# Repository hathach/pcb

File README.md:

# pcb — PCB projects home

One repo, Adafruit-style: every board lives in its own directory here,
alongside the shared knowledge, footprints, and tooling that future
boards reuse. Board pico2_trace_motherboard's original 50-commit build
history is preserved on branch `archive/pico2-original`.

## Layout

| Entry                             | What                                                                                                                                                               |
| --------------------------------- | ------------------------------------------------------------------------------------------------------------------------------------------------------------------ |
| `pico2_trace_motherboard/`        | Board #1: Pico 2 SWD+ETM trace carrier + TinyUSB dev/test bench (RP2350, 2-layer). Ordered: JLCPCB **W2026073018593887**, 2026-07-30, 5 PCB / 2 assembled, $81.27. |
| `docs/pipeline.md`                | The netlist-driven KiCad pipeline + gate battery + how to bootstrap board #2.                                                                                      |
| `docs/kicad-pcbnew-facts.md`      | Verified KiCad 9 scripting landmines (pcbnew API, kicad-cli, footprints).                                                                                          |
| `docs/parts-palette.md`           | LCSC/JLC-verified parts with tiers + JLC fee behavior.                                                                                                             |
| `docs/PICO2_TRACE_PCB_HANDOFF.md` | Origin brief for board #1 (fly-wire measurements, requirements).                                                                                                   |
| `lib/pcb.pretty/`                 | Audited shared footprints: USB-C C165948 lands (power-only + USB2-device renumbers), FTSH-110/105 1.27mm headers. Copy into each board's local `.pretty`.          |
| `tools/jlc-cdp/`                  | Chrome-DevTools JLCPCB ordering driver + wizard-trap playbook.                                                                                                     |
| `tools/board_semantic_compare.py` | Prove two `.kicad_pcb` are geometrically identical (regen gate).                                                                                                   |
| `tools/align_md_tables.py`        | Markdown table column aligner (house style).                                                                                                                       |

## Starting a new board

Read `docs/pipeline.md` — short version: copy `pico2_trace_motherboard/hw/`
wholesale, gut the board-specific tables, keep every helper and gate, seed
footprints from `lib/pcb.pretty/`, and regenerate-never-hand-nudge.

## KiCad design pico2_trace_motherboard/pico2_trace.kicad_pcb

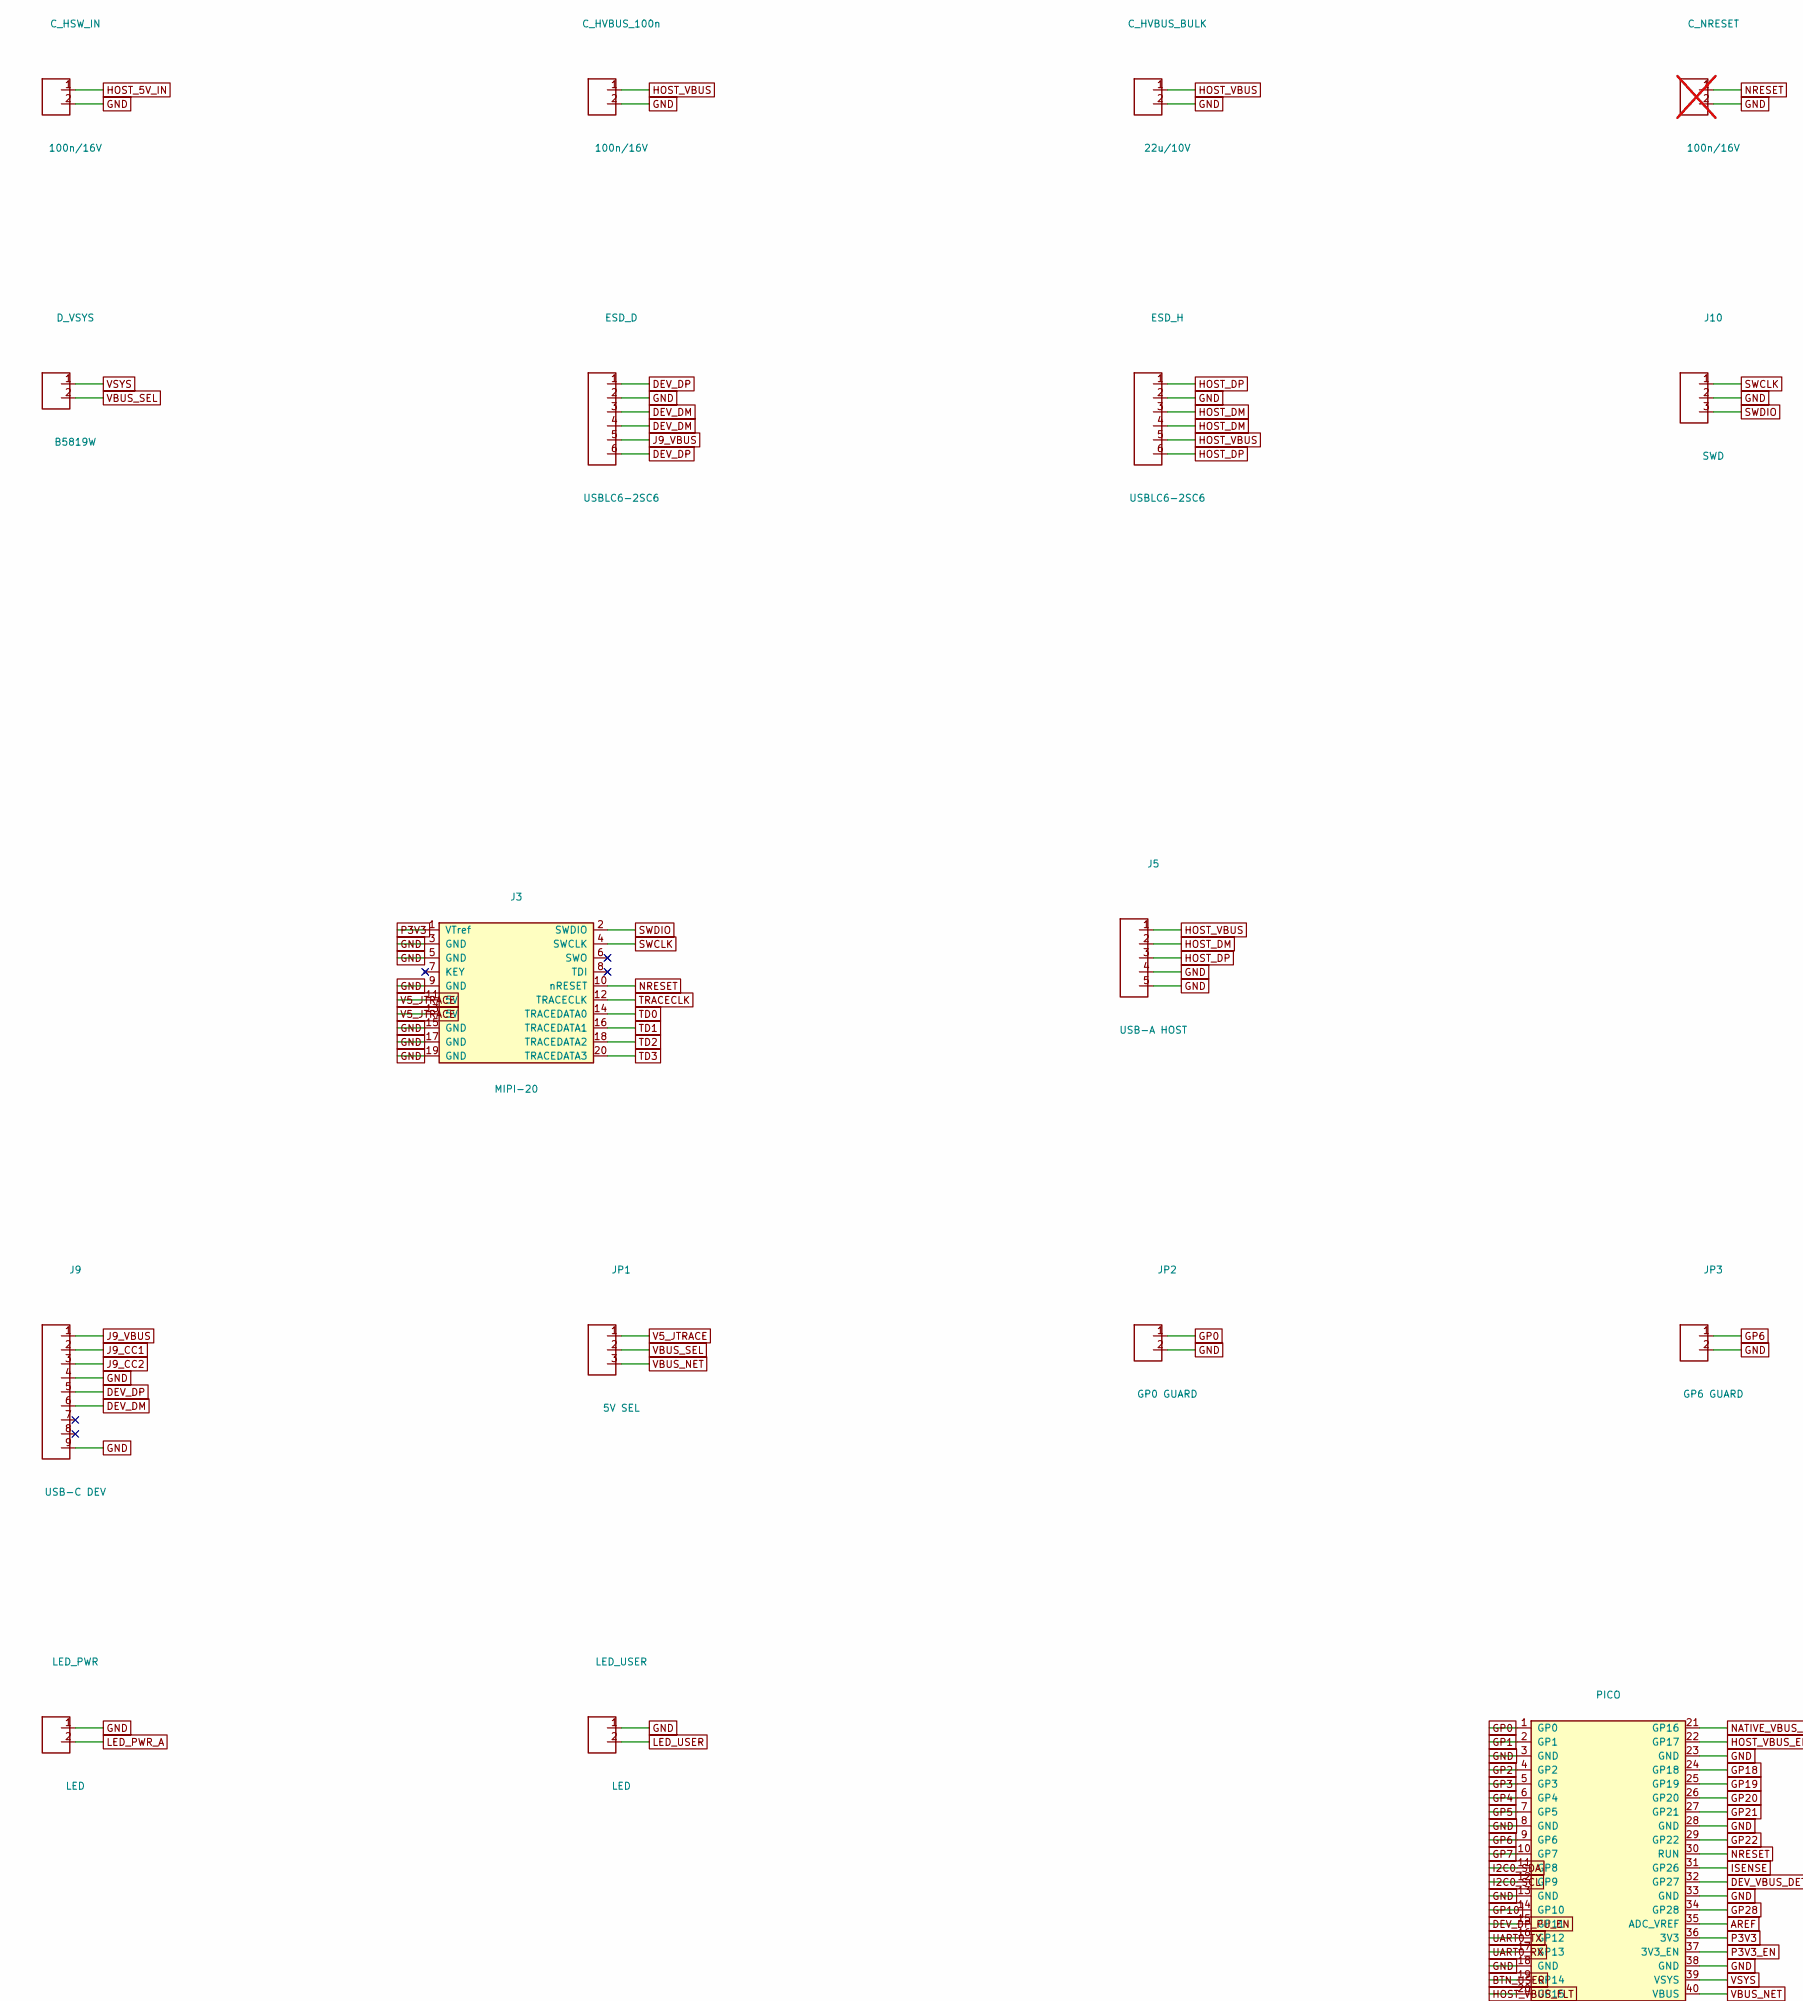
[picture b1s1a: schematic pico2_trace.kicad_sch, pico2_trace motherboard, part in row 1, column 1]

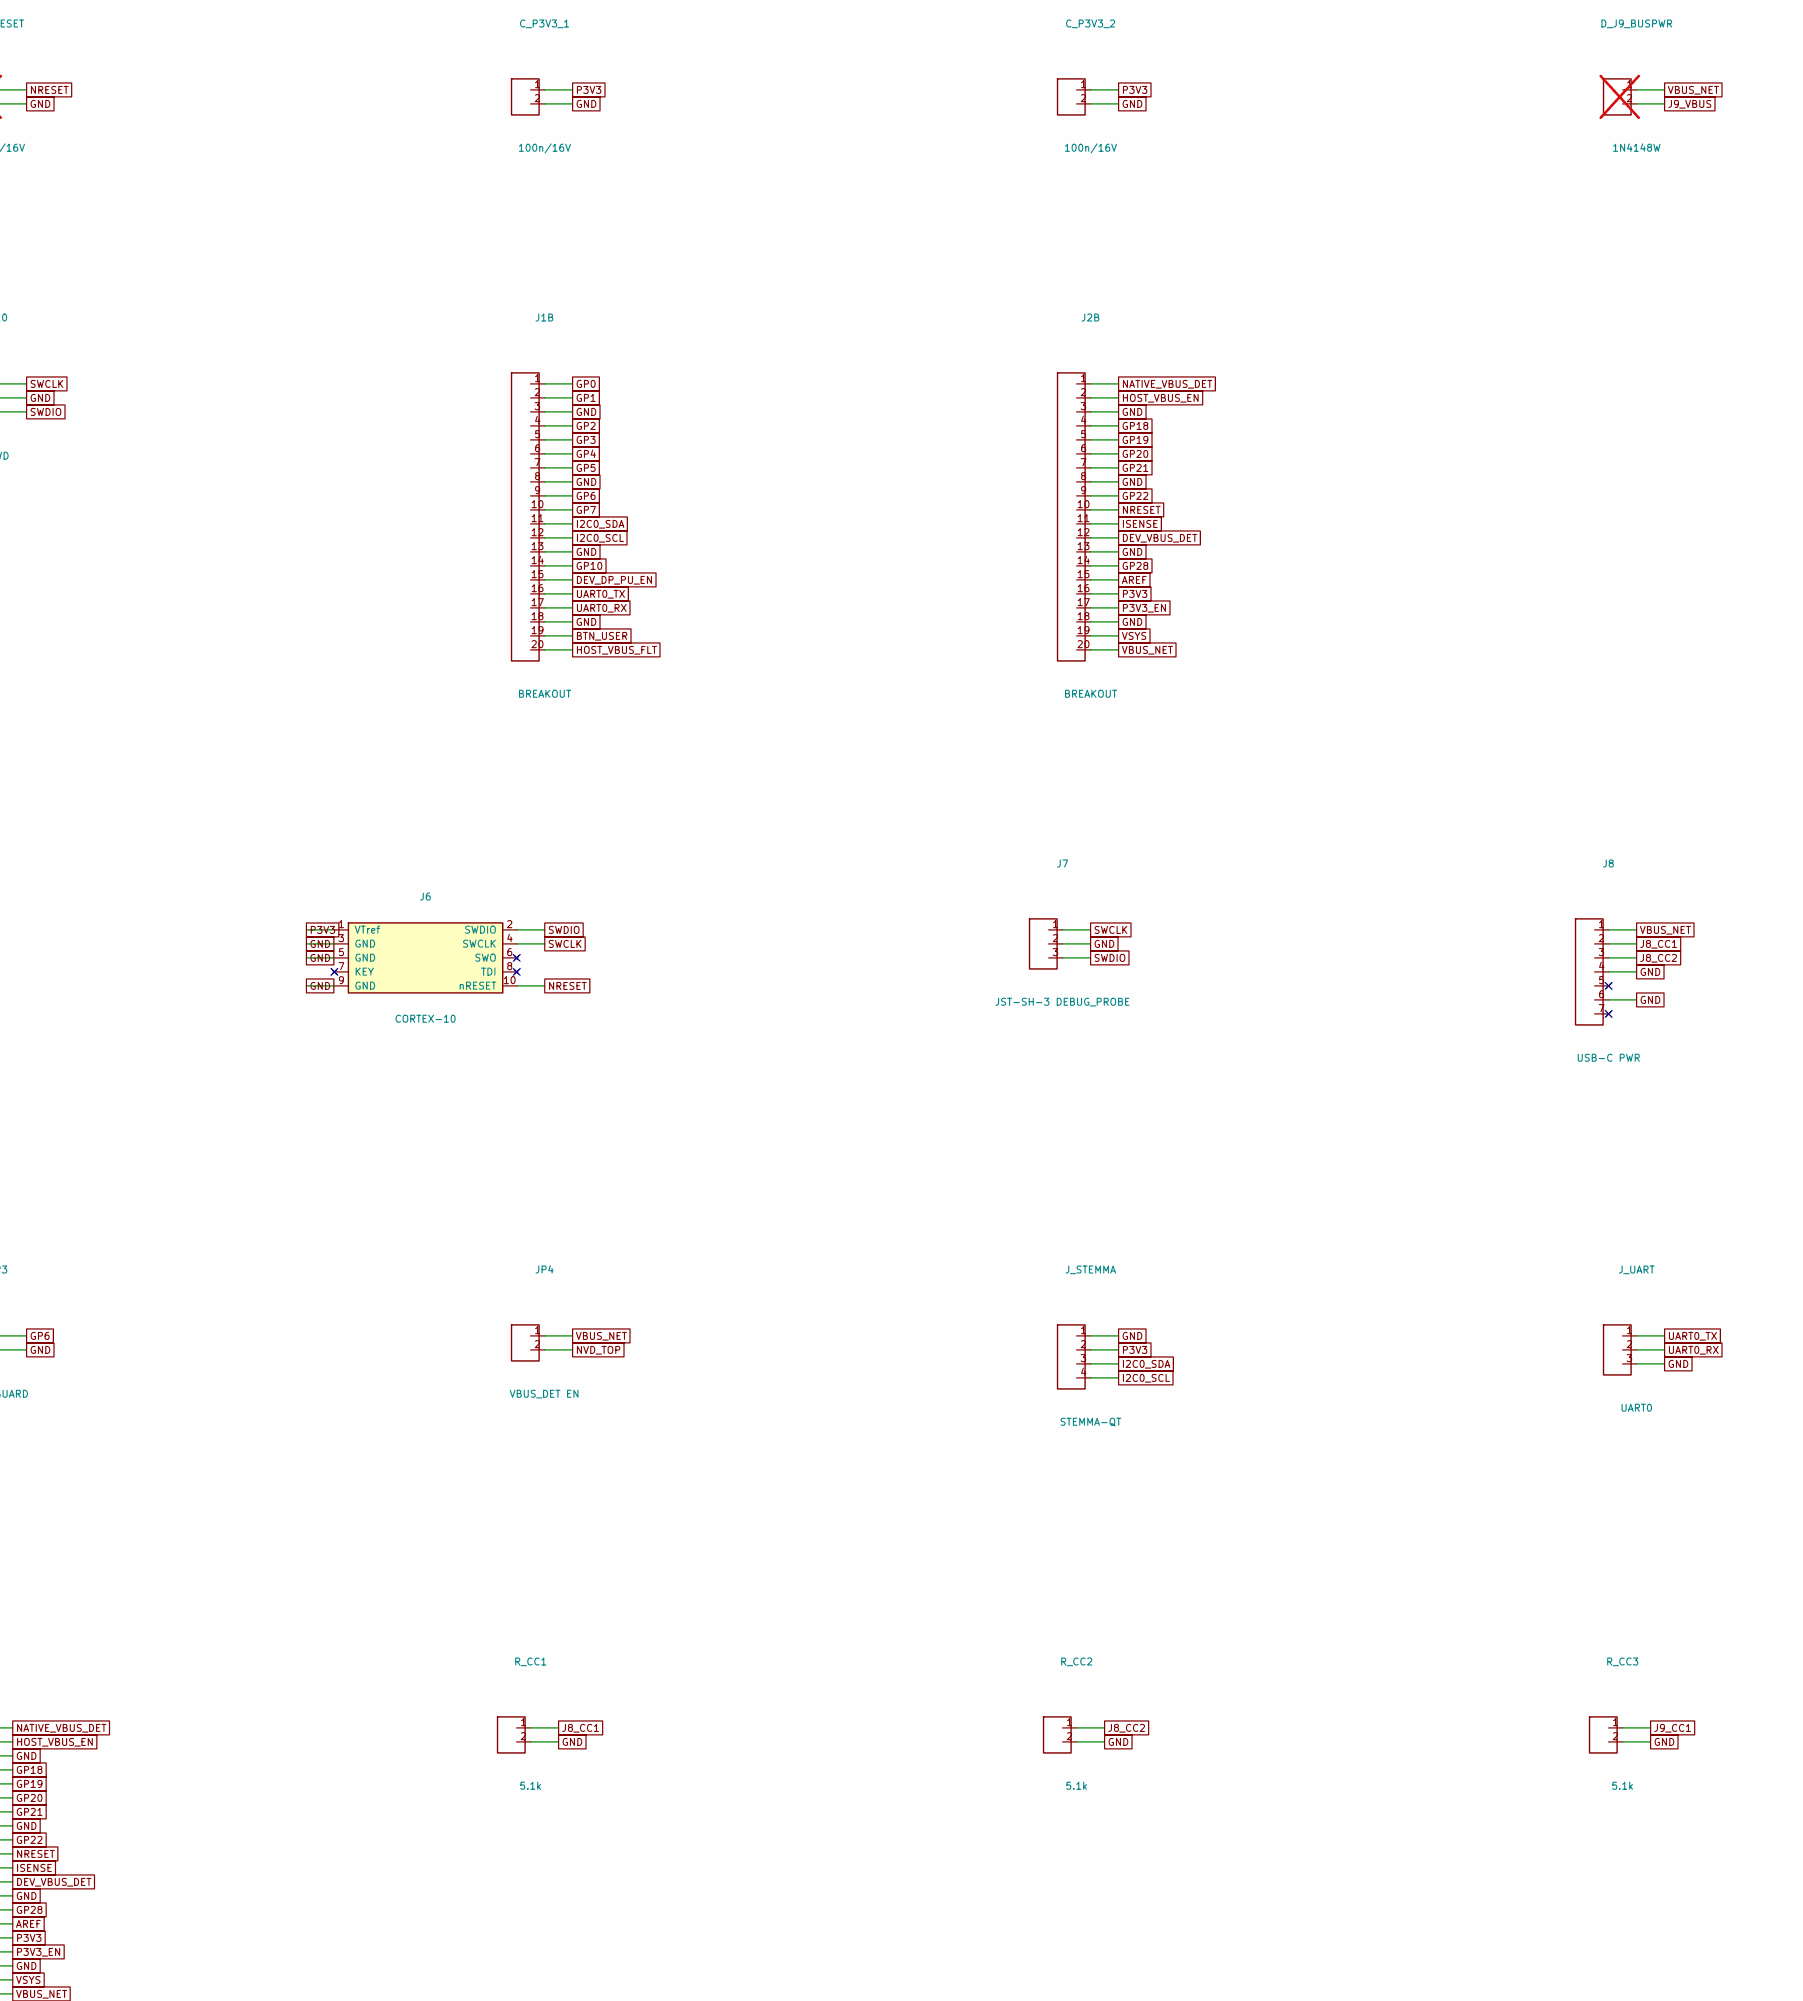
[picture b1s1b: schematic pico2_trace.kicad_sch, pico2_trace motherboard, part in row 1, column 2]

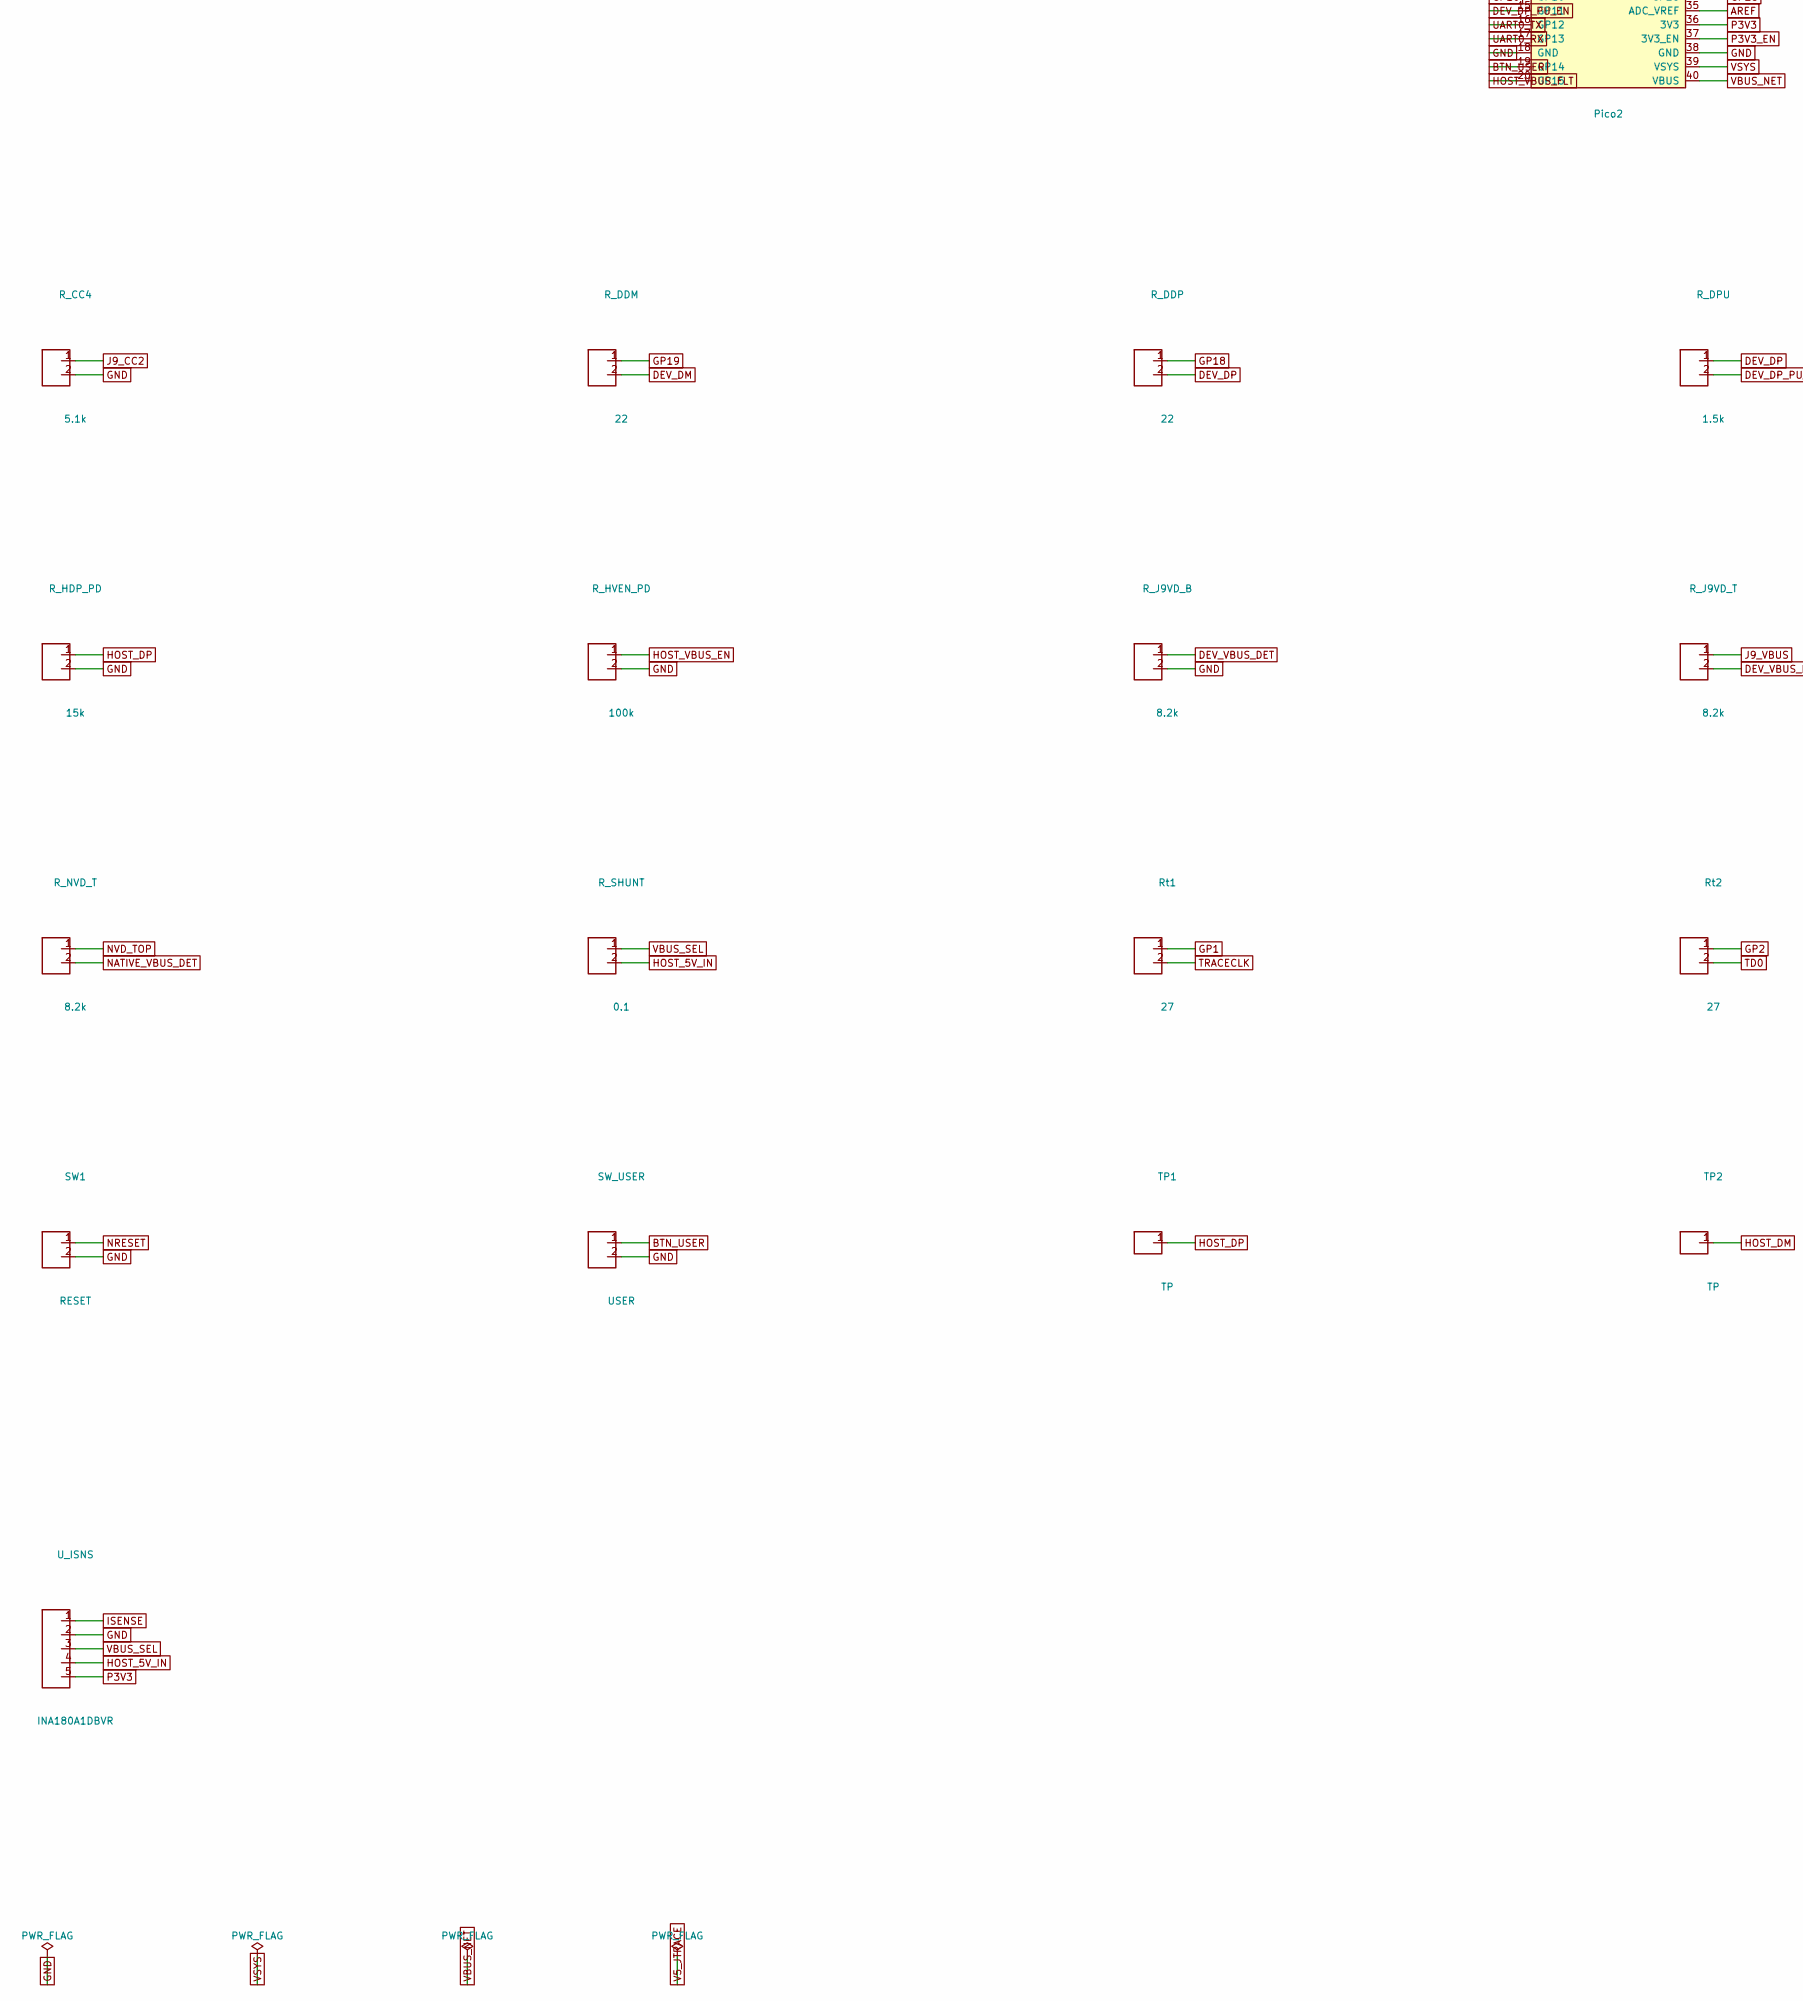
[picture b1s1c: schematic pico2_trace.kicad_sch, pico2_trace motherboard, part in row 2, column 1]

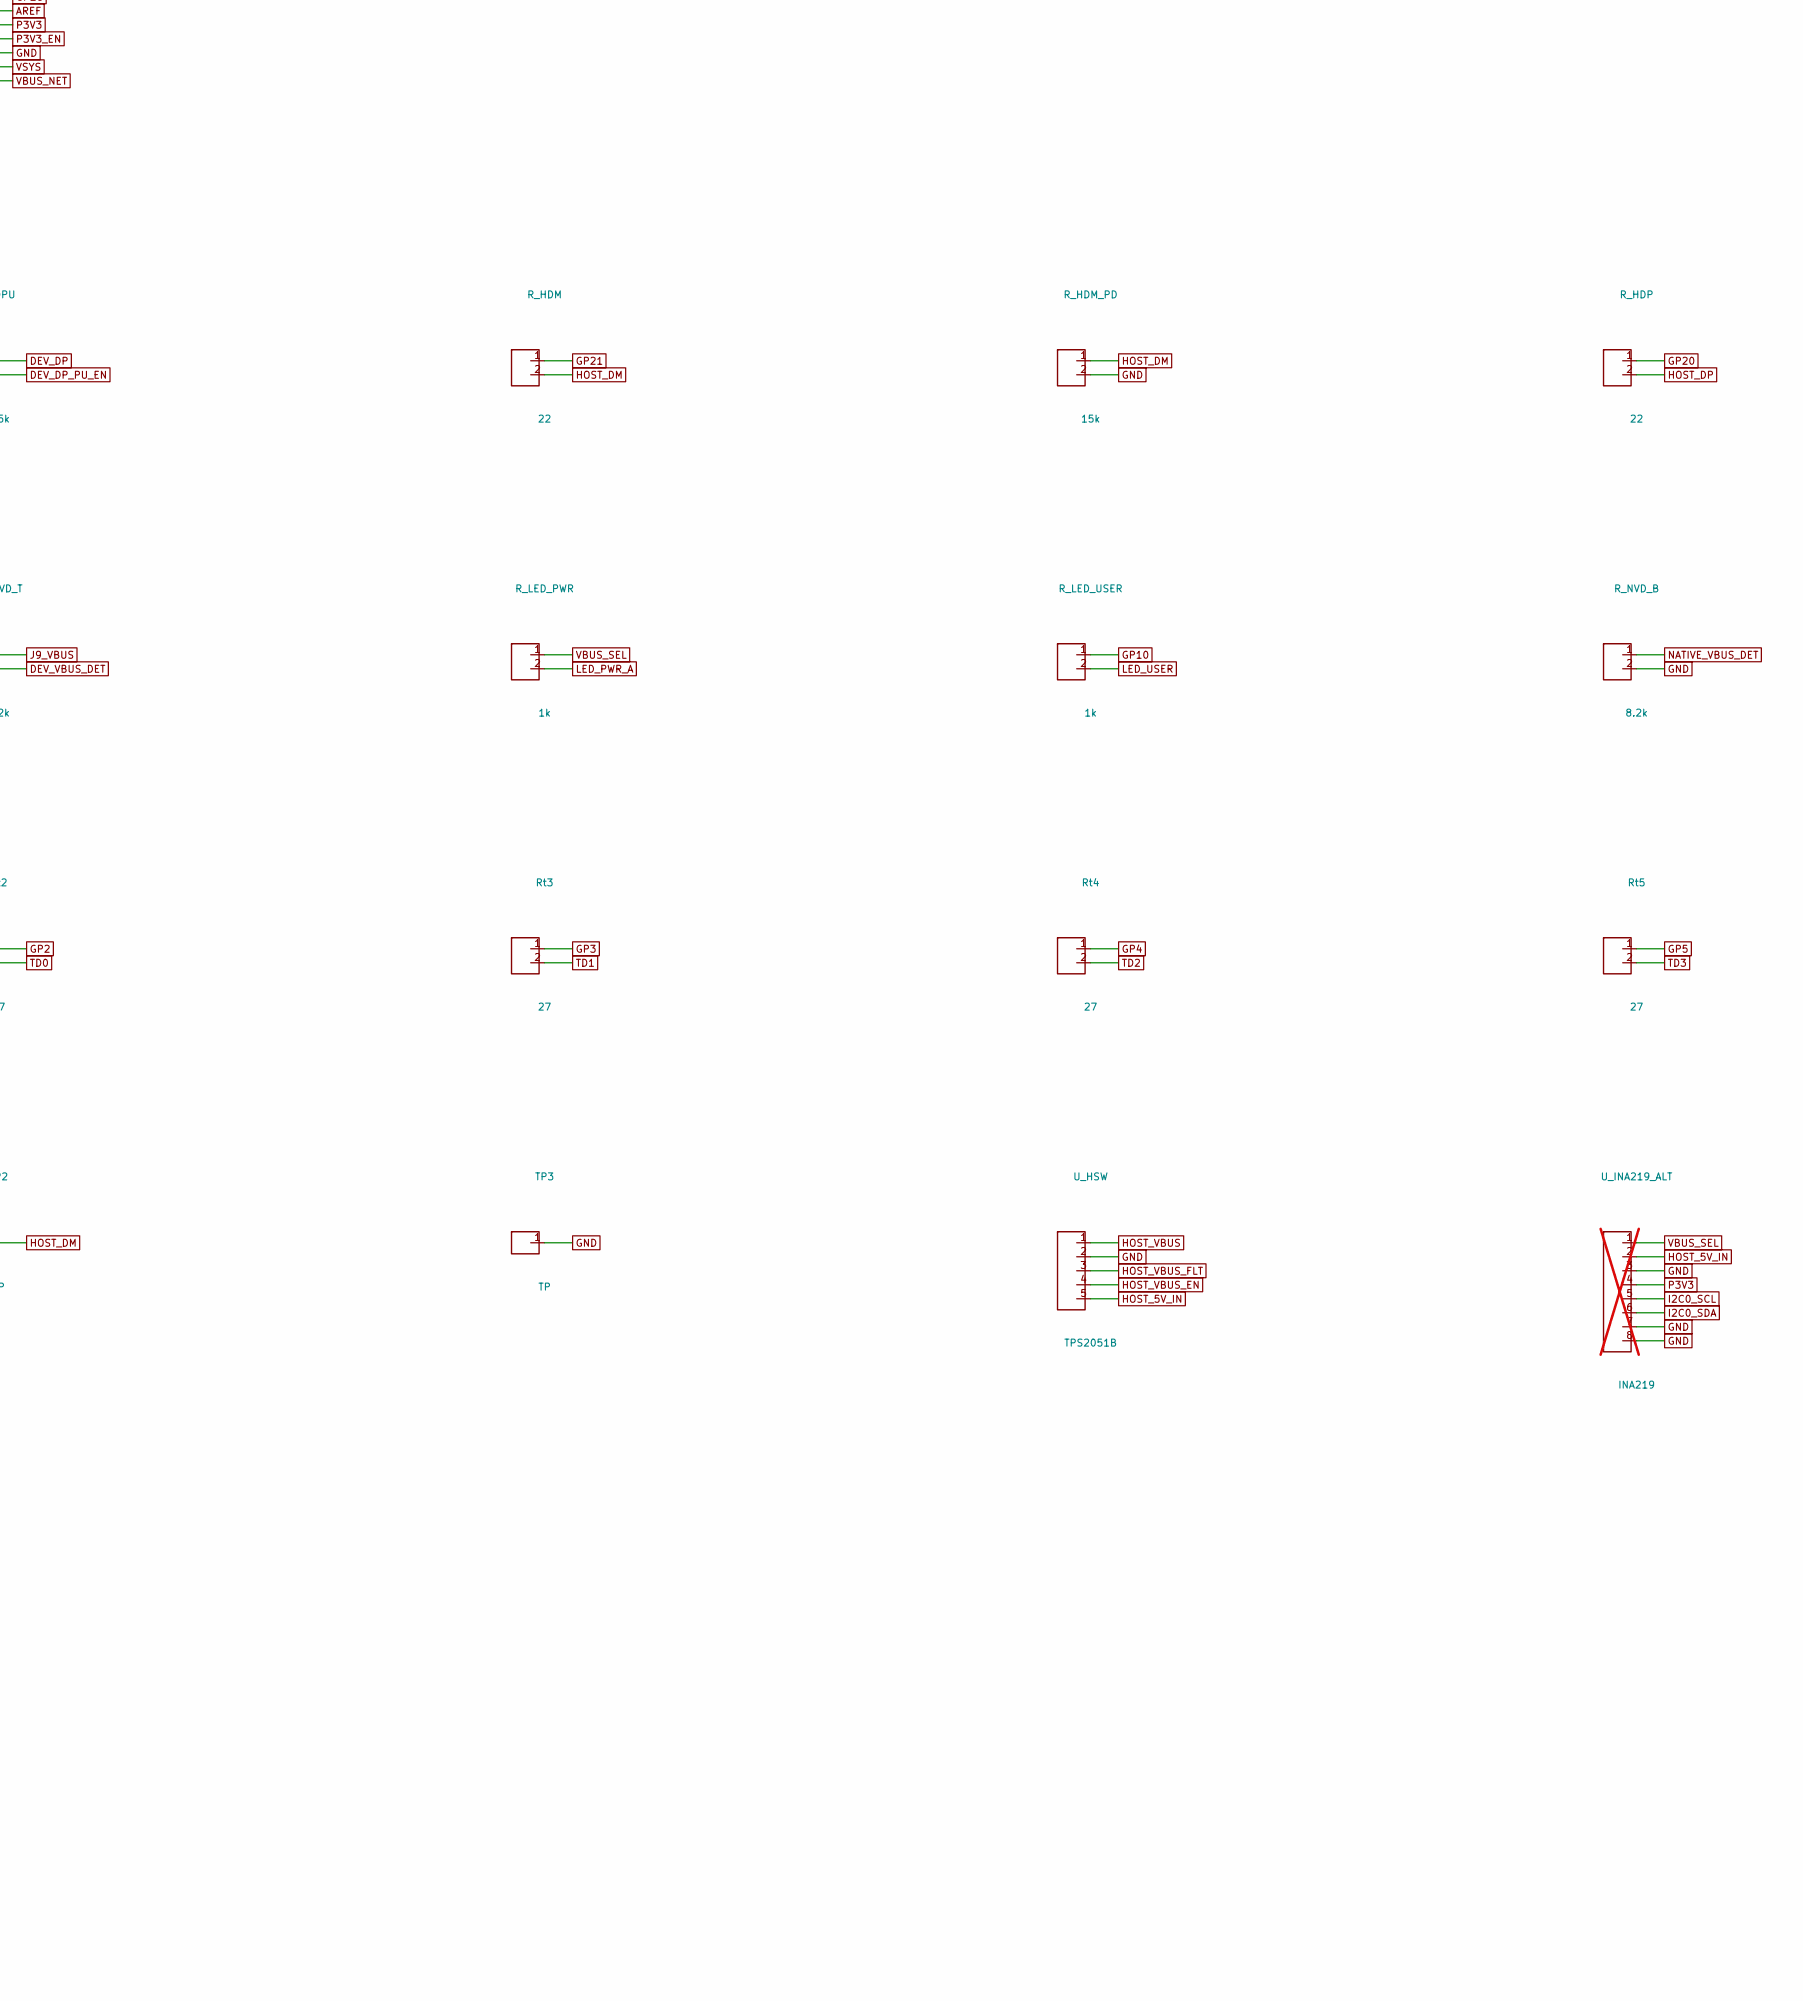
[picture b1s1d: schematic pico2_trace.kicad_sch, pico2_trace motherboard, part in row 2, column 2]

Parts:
C_HSW_IN: 100n/16V; C_0402_1005Metric
C_HVBUS_100n: 100n/16V; C_0402_1005Metric
C_HVBUS_BULK: 22u/10V; C_0805_2012Metric
C_NRESET: 100n/16V; C_0402_1005Metric; not fitted
C_P3V3_1, C_P3V3_2: 100n/16V; C_0402_1005Metric
D_J9_BUSPWR: 1N4148W; D_SOD-123; not fitted
D_VSYS: B5819W; D_SOD-123
ESD_D: USBLC6-2SC6; SOT-23-6
ESD_H: USBLC6-2SC6; SOT-23-6
J1B, J2B: BREAKOUT; PinSocket_1x20_P2.54mm_Vertical
J3: MIPI-20; FTSH-110-01-DV
J5: USB-A HOST; USB_A_Receptacle_GCT_USB1046
J6: CORTEX-10; FTSH-105-01-DV
J7: JST-SH-3 DEBUG_PROBE; JST_SH_SM03B-SRSS-TB_1x03-1MP_P1.00mm_Horizontal
J8: USB-C PWR; USB_C_PWR_HRO_TYPE-C-31-M-12
J9: USB-C DEV; USB_C_DEV_HRO_TYPE-C-31-M-12
J10: SWD; PinHeader_1x03_P2.54mm_Vertical
JP1: 5V SEL; PinHeader_1x03_P2.54mm_Vertical
JP2: GP0 GUARD; PinHeader_1x02_P2.54mm_Vertical
JP3: GP6 GUARD; PinHeader_1x02_P2.54mm_Vertical
JP4: VBUS_DET EN; PinHeader_1x02_P2.54mm_Vertical
J_STEMMA: STEMMA-QT; JST_SH_SM04B-SRSS-TB_1x04-1MP_P1.00mm_Horizontal
J_UART: UART0; PinHeader_1x03_P2.54mm_Vertical
LED_PWR: LED; LED_0603_1608Metric
LED_USER: LED; LED_0603_1608Metric
PICO: Pico2; RaspberryPi_Pico_Common_THT
R_CC1, R_CC2, R_CC3, R_CC4: 5.1k; R_0402_1005Metric
R_DDM: 22; R_0402_1005Metric
R_DDP: 22; R_0402_1005Metric
R_DPU: 1.5k; R_0402_1005Metric
R_HDM: 22; R_0402_1005Metric
R_HDM_PD: 15k; R_0402_1005Metric
R_HDP: 22; R_0402_1005Metric
R_HDP_PD: 15k; R_0402_1005Metric
R_HVEN_PD: 100k; R_0402_1005Metric
R_J9VD_B, R_J9VD_T: 8.2k; R_0402_1005Metric
R_LED_PWR: 1k; R_0402_1005Metric
R_LED_USER: 1k; R_0402_1005Metric
R_NVD_B: 8.2k; R_0402_1005Metric
R_NVD_T: 8.2k; R_0402_1005Metric
R_SHUNT: 0.1; R_1206_3216Metric
Rt1, Rt2, Rt3, Rt4, Rt5: 27; R_0402_1005Metric
SW1: RESET; SW_SPST_B3S-1000
SW_USER: USER; SW_SPST_B3S-1000
TP1, TP2, TP3: TP; TestPoint_Pad_D1.5mm
U_HSW: TPS2051B; SOT-23-5
U_INA219_ALT: INA219; SOT-23-8; not fitted
U_ISNS: INA180A1DBVR; SOT-23-5

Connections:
AREF: J2B.15, PICO.35 (ADC_VREF)
BTN_USER: J1B.19, PICO.19 (GP14), SW_USER.1
DEV_DM: ESD_D.3, ESD_D.4, J9.6, R_DDM.2
DEV_DP: ESD_D.1, ESD_D.6, J9.5, R_DDP.2, R_DPU.1
DEV_DP_PU_EN: J1B.15, PICO.15 (GP11), R_DPU.2
DEV_VBUS_DET: J2B.12, PICO.32 (GP27), R_J9VD_B.1, R_J9VD_T.2
GP0: J1B.1, JP2.1, PICO.1 (GP0)
GP1: J1B.2, PICO.2 (GP1), Rt1.1
GP2: J1B.4, PICO.4 (GP2), Rt2.1
GP3: J1B.5, PICO.5 (GP3), Rt3.1
GP4: J1B.6, PICO.6 (GP4), Rt4.1
GP5: J1B.7, PICO.7 (GP5), Rt5.1
GP6: J1B.9, JP3.1, PICO.9 (GP6)
GP7: J1B.10, PICO.10 (GP7)
GP10: J1B.14, PICO.14 (GP10), R_LED_USER.1
GP18: J2B.4, PICO.24 (GP18), R_DDP.1
GP19: J2B.5, PICO.25 (GP19), R_DDM.1
GP20: J2B.6, PICO.26 (GP20), R_HDP.1
GP21: J2B.7, PICO.27 (GP21), R_HDM.1
GP22: J2B.9, PICO.29 (GP22)
GP28: J2B.14, PICO.34 (GP28)
HOST_5V_IN: C_HSW_IN.1, R_SHUNT.2, U_HSW.5, U_INA219_ALT.2, U_ISNS.4
HOST_DM: ESD_H.3, ESD_H.4, J5.2, R_HDM.2, R_HDM_PD.1, TP2.1
HOST_DP: ESD_H.1, ESD_H.6, J5.3, R_HDP.2, R_HDP_PD.1, TP1.1
HOST_VBUS: C_HVBUS_100n.1, C_HVBUS_BULK.1, ESD_H.5, J5.1, U_HSW.1
HOST_VBUS_EN: J2B.2, PICO.22 (GP17), R_HVEN_PD.1, U_HSW.4
HOST_VBUS_FLT: J1B.20, PICO.20 (GP15), U_HSW.3
I2C0_SCL: J1B.12, J_STEMMA.4, PICO.12 (GP9), U_INA219_ALT.5
I2C0_SDA: J1B.11, J_STEMMA.3, PICO.11 (GP8), U_INA219_ALT.6
ISENSE: J2B.11, PICO.31 (GP26), U_ISNS.1
J8_CC1: J8.2, R_CC1.1
J8_CC2: J8.3, R_CC2.1
J9_CC1: J9.2, R_CC3.1
J9_CC2: J9.3, R_CC4.1
J9_VBUS: D_J9_BUSPWR.2, ESD_D.5, J9.1, R_J9VD_T.1
LED_PWR_A: LED_PWR.2, R_LED_PWR.2
LED_USER: LED_USER.2, R_LED_USER.2
NATIVE_VBUS_DET: J2B.1, PICO.21 (GP16), R_NVD_B.1, R_NVD_T.2
NRESET: C_NRESET.1, J2B.10, J3.10 (nRESET), J6.10 (nRESET), PICO.30 (RUN), SW1.1
NVD_TOP: JP4.2, R_NVD_T.1
P3V3: C_P3V3_1.1, C_P3V3_2.1, J2B.16, J3.1 (VTref), J6.1 (VTref), J_STEMMA.2, PICO.36 (3V3), U_INA219_ALT.4, U_ISNS.5
P3V3_EN: J2B.17, PICO.37 (3V3_EN)
SWCLK: J3.4 (SWCLK), J6.4 (SWCLK), J7.1, J10.1
SWDIO: J3.2 (SWDIO), J6.2 (SWDIO), J7.3, J10.3
TD0: J3.14 (TRACEDATA0), Rt2.2
TD1: J3.16 (TRACEDATA1), Rt3.2
TD2: J3.18 (TRACEDATA2), Rt4.2
TD3: J3.20 (TRACEDATA3), Rt5.2
TRACECLK: J3.12 (TRACECLK), Rt1.2
UART0_RX: J1B.17, J_UART.2, PICO.17 (GP13)
UART0_TX: J1B.16, J_UART.1, PICO.16 (GP12)
VBUS_SEL: D_VSYS.2, JP1.2, R_LED_PWR.1, R_SHUNT.1, U_INA219_ALT.1, U_ISNS.3

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
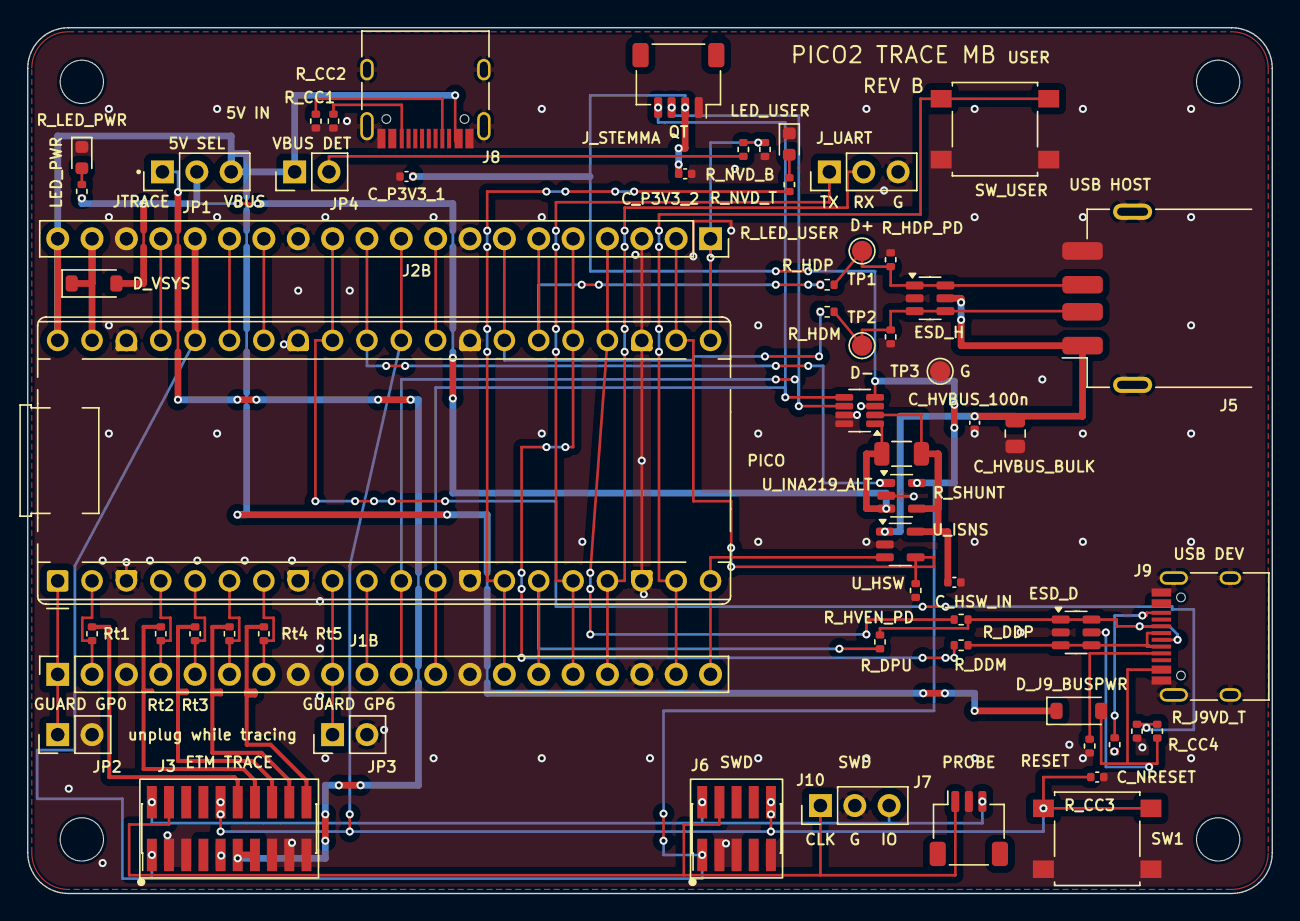
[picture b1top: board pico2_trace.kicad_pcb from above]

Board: 2 copper layers, 92.0 x 64.0 mm, 64 parts (0 on the bottom side), 56 nets.

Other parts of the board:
MH1, MH2, MH3, MH4: MountingHole_3.2mm_M3

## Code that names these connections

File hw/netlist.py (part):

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    element (Rt1-5 for the trace bus, the 22R USB series resistors, the LED
    series resistors), PICO's own pin keeps a bare "GPn" net; the *far* side
    of that element carries the function name (e.g. "GP1" -Rt1-> "TRACECLK",
    "GP20" -R_HDP-> "HOST_DP"). PINMAP hops through that element to report
    the function name for the GPIO.
  - Guard pins (GP0/GP6) are the same source-series shape with GND on the far
    side: PICO's own pin keeps a bare "GPn" net (distinct per pin) and a
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    function name, PINMAP derives the literal label "GUARD" for this shape
    instead of hopping to it.
  - For a GPIO that *is itself* the function node -- a resistor-divider
    midpoint (ISENSE, NATIVE_VBUS_DET, DEV_VBUS_DET), or a pin with no series
    element at all (HOST_VBUS_EN/FLT, I2C/UART/button pins, DEV_DP_PU_EN) --
    PICO's own pin should be named with the function directly (e.g.
    "NATIVE_VBUS_DET"). PINMAP only ever hops (source-series or guard) when
    the PICO-side net itself is a bare "GPn"-style name; that keeps divider
    midpoints (two hop-class neighbors: top leg + GND leg) out of the
    one-neighbor hop path, and stops a named function net from hopping just
    because a resistor happens to be its only neighbor (e.g. DEV_DP_PU_EN
    must NOT hop to "DEV_DP" through R_DPU -- R_DPU is a pull-up, not a
    source-series element on DEV_DP_PU_EN's own GPIO).
"""

from __future__ import annotations
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_add(Part("C_NRESET", "100n/16V", "c0402", _pins("1", "2"), dnp=True))

# --- USB D+/D- series resistors (22R) --------------------------------------
_add(Part("R_HDP", "22", "r0402", _pins("1", "2")))   # host D+ series (GP20 -> HOST_DP)
_add(Part("R_HDM", "22", "r0402", _pins("1", "2")))   # host D- series (GP21 -> HOST_DM)
_add(Part("R_DDP", "22", "r0402", _pins("1", "2")))   # device D+ series (GP18 -> DEV_DP)
_add(Part("R_DDM", "22", "r0402", _pins("1", "2")))   # device D- series (GP19 -> DEV_DM)

# --- Host D+/D- pulldowns (15k) ------------------------------------------
_add(Part("R_HDP_PD", "15k", "r0402", _pins("1", "2")))   # HOST_DP -> GND
_add(Part("R_HDM_PD", "15k", "r0402", _pins("1", "2")))   # HOST_DM -> GND

# --- Device D+ pull-up (1.5k), firmware soft-connect via GP11 --------------
_add(Part("R_DPU", "1.5k", "r0402", _pins("1", "2")))
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# --- LEDs + series resistors -------------------------------------------
# Placeholder 1k series value; final current-limit value is a BOM tuning
# detail (Task 17), not a connectivity concern.
_add(Part("LED_USER", "LED", "led0603", _pins("1", "2")))
_add(Part("LED_PWR", "LED", "led0603", _pins("1", "2")))
_add(Part("R_LED_USER", "1k", "r0402", _pins("1", "2")))
_add(Part("R_LED_PWR", "1k", "r0402", _pins("1", "2")))
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# D_J9_BUSPWR: optional J9-VBUS -> VBUS_NET bus-power diode (DESIGN SS8.2/SS14).
_add(Part("D_J9_BUSPWR", "1N4148W", "sod123", _pins("1", "2"), dnp=True))
# D_VSYS (Task 18, user-approved DESIGN SS7 restore): Schottky diode-ORs
# VBUS_SEL into VSYS so JP1=JTRACE can power the Pico without touching pin
# 40/VBUS_NET (which must stay the micro-USB VBUS node for OTG-host use --
# see the wiring comment below). Same sod123 footprint/pad convention as
# D_J9_BUSPWR: pad1=CATHODE, pad2=ANODE (verified against the footprint's
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# --------------------------------------------------------------------------
# Task 4: power & ground nets
# --------------------------------------------------------------------------
# JP1 (DESIGN SS7): pin1=V5_JTRACE (J-Trace 5V), pin3=VBUS_NET (the single
# hard-tied USB-side node: PICO pin 40 / module micro-USB / J8 / external-5V
# injection -- never switch-broken), pin2=VBUS_SEL is JP1's *selected*
# output (board 5V rail) that feeds the host load switch + power LED.
PARTS["JP1"].pins.update({"1": "V5_JTRACE", "2": "VBUS_SEL", "3": "VBUS_NET"})

PARTS["PICO"].pins.update({
    "40": "VBUS_NET",   # SS7: hard-tied USB-side node, never switched
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# NOTE (Task 6): IN's net is retargeted from VBUS_SEL to HOST_5V_IN below --
# Task 6 inserts R_SHUNT upstream of IN for current sensing (SS10). This
# test's assertions don't cover IN's net so the change is safe (verified).
PARTS["U_HSW"].pins.update({"IN": "VBUS_SEL", "OUT": "HOST_VBUS", "GND": "GND"})
PARTS["J5"].pins.update({"VBUS": "HOST_VBUS", "GND": "GND"})
# J5 shell (Task 18 pre-fab review): pad "5" is J5's two PTH mounting/shell
# posts (mechanical, not a signal pad -- like J8/J9's own shield pad, no
# logical name was ever given it, so it's set directly by footprint pad
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PARTS["J5"].pins["5"] = "GND"

# HOST_VBUS bulk + decoupling caps at the connector (SS8.1).
PARTS["C_HVBUS_BULK"].pins.update({"1": "HOST_VBUS", "2": "GND"})
PARTS["C_HVBUS_100n"].pins.update({"1": "HOST_VBUS", "2": "GND"})

# J8 (Type-C power-only, renumbered pads -- see the Part definition): VBUS
# pad group -> VBUS_NET, GND pad group -> GND. CC1/CC2 get their own nets so
# the Rd resistors are a real series element (net-naming convention above).
PARTS["J8"].pins.update({"1": "VBUS_NET", "4": "GND", "2": "J8_CC1", "3": "J8_CC2"})
PARTS["R_CC1"].pins.update({"1": "J8_CC1", "2": "GND"})
PARTS["R_CC2"].pins.update({"1": "J8_CC2", "2": "GND"})

# Debug-jack + peripheral + ESD grounds (signal pins left for their own tasks).
PARTS["J7"].pins["2"] = "GND"          # JST-SH-3 DEBUG_PROBE: 1=SWCLK,2=GND,3=SWDIO
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PARTS["J_STEMMA"].pins["1"] = "GND"    # Adafruit order: 1=GND,2=3V3,3=SDA,4=SCL
PARTS["ESD_H"].pins["GND"] = "GND"
PARTS["ESD_D"].pins["GND"] = "GND"
PARTS["SW1"].pins["2"] = "GND"         # RESET button: 1->NRESET (Task 5), 2->GND

# Power LED: VBUS_SEL -> R_LED_PWR -> LED_PWR anode; cathode -> GND. LED pad
# numbering follows the KiCad "LED" symbol default (pad1=K/cathode,
# pad2=A/anode) -- keep LED_USER (Task 7) consistent with this convention.
PARTS["R_LED_PWR"].pins.update({"1": "VBUS_SEL", "2": "LED_PWR_A"})
PARTS["LED_PWR"].pins.update({"2": "LED_PWR_A", "1": "GND"})


# --------------------------------------------------------------------------
# Task 5: debug & trace nets
# --------------------------------------------------------------------------
# VTREF ruling: there is no separate "VTREF" net -- PICO "36" is already on
# P3V3 (Task 4). J3/J6 pin 1 (VTref) just join that same net.
PARTS["J3"].pins["1"] = "P3V3"
PARTS["J6"].pins["1"] = "P3V3"

# SWD fan-out (DESIGN SS5.1-5.3): J7 (SWCLK/GND/SWDIO, GND done in Task 4)
# and J3/J6 pins 2/4 all share the SWDIO/SWCLK nets.
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# J6 grounds deferred from Task 4 (ruling): pins 3/5/9 -> GND.
PARTS["J6"].pins.update({"3": "GND", "5": "GND", "9": "GND"})

# NRESET (DESIGN SS5.1/5.2: nRESET = RUN, pin 30): PICO -> J3/J6 pin 10 ->
# SW1 side 1; SW1 side 2 -> GND (Task 4). Debounce cap across SW1.
PARTS["PICO"].pins["30"] = "NRESET"
PARTS["J3"].pins["10"] = "NRESET"
PARTS["J6"].pins["10"] = "NRESET"
PARTS["SW1"].pins["1"] = "NRESET"
PARTS["C_NRESET"].pins.update({"1": "NRESET", "2": "GND"})

# SWO/KEY/TDI: RP2350 has no SWO, KEY/TDI are unused on this bus -- NC on
# both debug connectors (DESIGN SS5.1/5.2, pins 6/7/8).
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# fitted at the socket pin) -> function net -> J3. GPn stays a bare net on
# the PICO/socket side per the module net-naming convention.
PARTS["PICO"].pins.update({"2": "GP1", "4": "GP2", "5": "GP3", "6": "GP4", "7": "GP5"})
PARTS["Rt1"].pins.update({"1": "GP1", "2": "TRACECLK"})
PARTS["Rt2"].pins.update({"1": "GP2", "2": "TD0"})
PARTS["Rt3"].pins.update({"1": "GP3", "2": "TD1"})
PARTS["Rt4"].pins.update({"1": "GP4", "2": "TD2"})
PARTS["Rt5"].pins.update({"1": "GP5", "2": "TD3"})
PARTS["J3"].pins.update({"12": "TRACECLK", "14": "TD0", "16": "TD1", "18": "TD2", "20": "TD3"})

# Guard pins (DESIGN SS5.4/SS6): GP0 (pin 1) / GP6 (pin 9) each get their own
# 2-pin jumper straight to GND (JP2/JP3, default fitted). These are two
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# J5, with 15k pulldowns and ESD_H across the pair. GPn stays a bare net on
# the PICO/socket side (source-series convention, same as the trace bus).
PARTS["PICO"].pins.update({"26": "GP20", "27": "GP21"})
PARTS["R_HDP"].pins.update({"1": "GP20", "2": "HOST_DP"})
PARTS["R_HDM"].pins.update({"1": "GP21", "2": "HOST_DM"})
PARTS["R_HDP_PD"].pins.update({"1": "HOST_DP", "2": "GND"})
PARTS["R_HDM_PD"].pins.update({"1": "HOST_DM", "2": "GND"})
PARTS["J5"].pins.update({"DP": "HOST_DP", "DM": "HOST_DM"})
# ESD_H: IO1/IO1B are the same internal channel (feed-through pads), likewise
# IO2/IO2B -- so one channel per line: IO1/IO1B -> HOST_DP, IO2/IO2B -> HOST_DM.
PARTS["ESD_H"].pins.update({
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    "VBUS": "HOST_VBUS",
})
# Probe points (DESIGN SS8.1, fixes G-3): TP1/TP2/TP3 on D+/D-/GND at the port.
PARTS["TP1"].pins["1"] = "HOST_DP"
PARTS["TP2"].pins["1"] = "HOST_DM"
PARTS["TP3"].pins["1"] = "GND"

# --- Host VBUS switch control (DESIGN SS6/SS8.1): EN/FLG *are* the function
# node on the PICO side (no series element), per the guard-net docstring case.
PARTS["PICO"].pins.update({"22": "HOST_VBUS_EN", "20": "HOST_VBUS_FLT"})
PARTS["U_HSW"].pins.update({"EN": "HOST_VBUS_EN", "FLG": "HOST_VBUS_FLT"})

# --- Current sense (DESIGN SS8.1/SS10): shunt placed *upstream* of U_HSW so
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

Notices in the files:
hw/netlist.py:
whose datasheet pinout matters get logical names + a padmap documenting the
real pad order (comments cite the datasheet figure consulted).
